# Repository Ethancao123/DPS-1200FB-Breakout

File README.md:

# DPS-1200FB-Breakout

Breakout board and power switch for the HP DPS-1200FB Power Supply

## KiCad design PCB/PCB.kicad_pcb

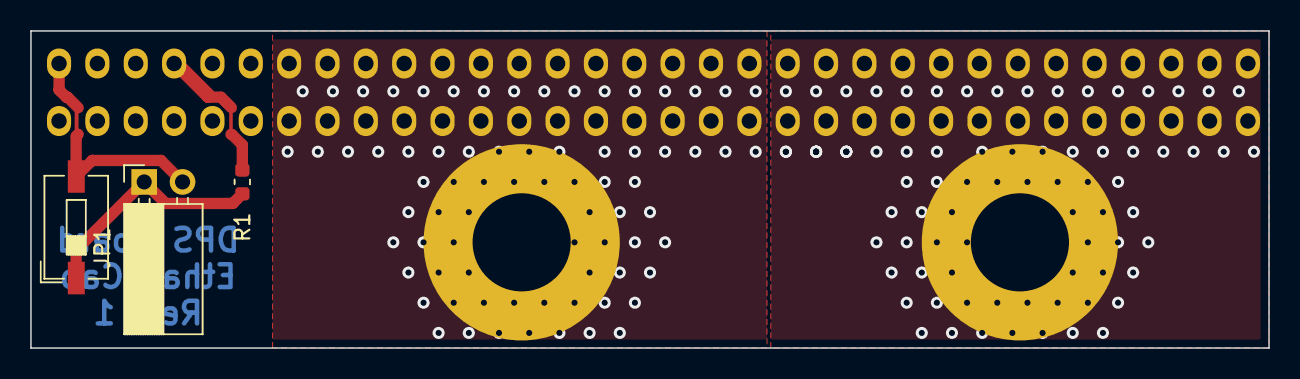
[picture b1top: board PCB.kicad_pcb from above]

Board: 2 copper layers, 82.0 x 21.0 mm, 6 parts (1 on the bottom side), 5 nets.

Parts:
 : MountingHole_6.5mm_Pad
 #2: MountingHole_6.5mm_Pad
J1: TE1761468-1
JP1: Jumper_NC_Small; PinSocket_1x02_P2.54mm_Horizontal
R1: R470; R_0603_1608Metric
SW1: SW_DIP_x01; SW_DIP_SPSTx01_Slide_6.7x4.1mm_W6.73mm_P2.54mm_LowProfile_J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

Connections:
+12V: #2.1, J1.20, J1.21, J1.22, J1.23, J1.24, J1.25, J1.26, J1.27, J1.28, J1.29, J1.30, J1.31, J1.32, J1.33, J1.34, J1.35, J1.36, J1.37, J1.38, J1.39, J1.40, J1.41, J1.42, J1.43, J1.44, J1.45
GND: .1, J1.7, J1.8, J1.9, J1.10, J1.11, J1.12, J1.13, J1.14, J1.15, J1.16, J1.17, J1.18, J1.19, J1.46, J1.47, J1.48, J1.49, J1.50, J1.51, J1.52, J1.53, J1.54, J1.55, J1.56, J1.57, J1.58
unnamed: J1.1, JP1.2, SW1.2
unnamed: J1.4, R1.2
unnamed: JP1.1, R1.1, SW1.1

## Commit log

2021-12-04 Started schematic
2021-12-06 Started pcb
2021-12-07 PCB Done
2021-12-07 uploaded images
2021-12-11 Created production files
